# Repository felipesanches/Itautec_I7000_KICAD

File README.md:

Trabalho de levantamento empírico dos esquemáticos do computador Itautec I-7000.

De vez em quando eu atualizo os PDFs:
- i7000.pdf (placa-mãe principal)
- i7000_disk.pdf (placa da interface de controle de disquetes)
- há também uma placa "TELEX" mas não comecei ainda a levantar o esquema dela.

Mas na maior parte do tempo estou só editando no KICAD os arquivos de esquemáticos e PCB por enquanto. Estou tentando me dedicar algumas horas todos os dias para essa tarefa...

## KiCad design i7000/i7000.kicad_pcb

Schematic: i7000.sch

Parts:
C207, C227: C; C_Disc_D3.8mm_W2.6mm_P2.50mm
CN04: Conn_02x30_Counter_Clockwise; Pin_Header_Straight_2x30_Pitch2.54mm
CN05: Conn_02x07_Counter_Clockwise; DIP-14_W7.62mm_Socket
E01: NSC800D-4; DIP-40_W15.24mm
E02: Intel D8202A-1; DIP-40_W15.24mm
E03: M5L8259AP; DIP-28_W15.24mm
E04: 2732; DIP-24_W15.24mm_Socket
E05, E06: 74LS373; DIP-20_W7.62mm
E07: 74LS245; DIP-20_W7.62mm
E08: 74LS257; DIP-16_W7.62mm
E09, E10: 74LS273; DIP-20_W7.62mm
E11, E12: 74LS153; DIP-16_W7.62mm
E13: 74LS138; DIP-16_W7.62mm
E14: 74LS157; DIP-16_W7.62mm
E15: 74LS374; DIP-20_W7.62mm
E16, E17, E18, E19, E20, E21, E22, E23: MCM6665A; DIP-16_W7.62mm
E24, E25, E26: 74LS74; DIP-14_W7.62mm
E27, E28, E29, E38: 74LS04; DIP-14_W7.62mm
E30: 74LS02; DIP-14_W7.62mm
E31, E34: 74LS08; DIP-14_W7.62mm
E32, E33, E36: 74LS32; DIP-14_W7.62mm
E35: 74LS00; DIP-14_W7.62mm
E37: SN74LS07N; DIP-14_W7.62mm
F01: M5L8279P-5; DIP-40_W15.24mm
F02: M5L8253P-5; DIP-24_W15.24mm
F03: TMP8255AP-5; DIP-40_W15.24mm
F04: TMP8251AP; DIP-28_W15.24mm
F05: ADC0808; DIP-28_W15.24mm
F06, F07: 74LS138; DIP-16_W7.62mm
F08, F11, F12: 74LS74; DIP-14_W7.62mm
F9, F10: 74LS163; DIP-16_W7.62mm
F13: 74LS139; DIP-16_W7.62mm
F14: 74LS27; DIP-14_W7.62mm
F15: 74LS00; DIP-14_W7.62mm
F16: 74LS08; DIP-14_W7.62mm
F17: MC1488; DIP-14_W7.62mm
F18, F19: MC1489; DIP-14_W7.62mm
F20: 74LS02; DIP-14_W7.62mm
F21: 74LS04; DIP-14_W7.62mm
F22, F23: SN74LS07N; DIP-14_W7.62mm
G01: MC6845; DIP-40_W15.24mm
G02, G03, G04, G05, G06: 74LS157; DIP-16_W7.62mm
G07, G08: TMM2016AP; DIP-24_W15.24mm
G09, G12: 74LS273; DIP-20_W7.62mm
G10, G11: 74LS245; DIP-20_W7.62mm
G13: 74LS244; DIP-20_W7.62mm
G14: 2732; DIP-24_W15.24mm_Socket
G15, G16, G17: 74LS374; DIP-20_W7.62mm
G18: 74LS166; DIP-16_W7.62mm
G19: Conn_02x08_Counter_Clockwise; DIP-16_W7.62mm
G20, G21: 74LS153; DIP-16_W7.62mm
G22, G23: 74LS174; DIP-16_W7.62mm
G25, G27, G28: 74LS74; DIP-14_W7.62mm
G26: 74LS163; DIP-16_W7.62mm
G29: 74LS20; DIP-14_W7.62mm
G30, G33: 74LS04; DIP-14_W7.62mm
G31, G35: 74LS08; DIP-14_W7.62mm
G32, G34: 74LS32; DIP-14_W7.62mm
G36: 74LS86; DIP-14_W7.62mm
G37: 74128; DIP-14_W7.62mm
G38, G39: 74LS00; DIP-14_W7.62mm
G40, G41: 74S140; DIP-14_W7.62mm
JP03, JP04, JP05: Conn_01x03; Pin_Header_Straight_1x03_Pitch2.54mm
R29, R38, R82, R83: R; R_Axial_DIN0207_L6.3mm_D2.5mm_P10.16mm_Horizontal
XTA2, XTA3, XTA4: Crystal; Crystal_AT310_d3.0mm_l10.0mm_Horizontal_1EP_style2

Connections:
A0: CN04.49, E02.6 (AL0), E06.19 (O7)
A1: CN04.51, E02.8 (AL1), E06.16 (O6)
A2: CN04.50, E02.10 (AL2), E06.15 (O5), F07.1 (A0)
A3: CN04.11, E02.12 (AL3), E06.12 (O4), F07.2 (A1)
A4: CN04.16, E02.14 (AL4), E06.9 (O3), F07.3 (A2), F14.5
A5: CN04.44, E02.16 (AL5), E04.3 (A5), E06.6 (O2), E28.13
A6: CN04.45, E02.18 (AL6), E06.5 (O1), F14.13
A7: CN04.17, E06.2 (O0), E14.3 (I1a), F14.2, G03.14 (I0c)
A8: CN04.15, E02.5 (AH0), E05.19 (O7)
A9: CN04.46, E02.4 (AH1), E05.16 (O6)
A10: CN04.48, E02.3 (AH2), E05.15 (O5)
A11: CN04.12, E02.2 (AH3), E05.12 (O4), G06.13 (I1c)
A12: CN04.47, E02.1 (AH4), E05.9 (O3)
A13: CN04.18, E02.39 (AH5), E05.6 (O2), G06.14 (I0c)
A14: E05.5 (O1), E11.14 (S0), E12.14 (S0)
A15: E05.2 (O0), E11.2 (S1), E12.2 (S1)
CHARGEN_SERIAL_OUT: G18.13 (Qh), G33.1
CN04_07: CN04.7, E13.9 (O6)
CN04_08: CN04.8, E13.10 (O5)
CN04_09: CN04.9, E13.12 (O3)
CN04_10: CN04.10, E13.14 (O1)
CN04_14: CN04.14
CN04_19: CN04.19
CN04_20: CN04.20
CN04_34: CN04.34, E08.15 (OE)
CN04_41: CN04.41
CN04_42: CN04.42
CN04_43: CN04.43
CN04_52: CN04.52, E13.13 (O2)
CN04_53: CN04.53, E13.11 (O4)
CN04_54: CN04.54, E13.7 (O7)
CN05_14: CN05.14, E32.8
CPU_A8: E01.1 (A8), E05.18 (D7)
CPU_A9: E01.2 (A9), E05.17 (D6)
CPU_A10: E01.3 (A10), E05.14 (D5)
CPU_A11: E01.4 (A11), E05.13 (D4)
CPU_A12: E01.5 (A12), E05.8 (D3)
CPU_A13: E01.6 (A13), E05.7 (D2)
CPU_A14: E01.7 (A14), E05.4 (D1)
CPU_A15: E01.8 (A15), E05.3 (D0)
CPU_AD0: E01.12 (AD0), E06.18 (D7), E07.9 (A7)
CPU_AD1: E01.13 (AD1), E06.17 (D6), E07.8 (A6)
CPU_AD2: E01.14 (AD2), E06.14 (D5), E07.7 (A5)
CPU_AD3: E01.15 (AD3), E06.13 (D4), E07.6 (A4)
CPU_AD4: E01.16 (AD4), E06.8 (D3), E07.5 (A3)
CPU_AD5: E01.17 (AD5), E06.7 (D2), E07.4 (A2)
CPU_AD6: E01.18 (AD6), E06.4 (D1), E07.3 (A1)
CPU_AD7: E01.19 (AD7), E06.3 (D0), E07.2 (A0)
D0: CN04.57, E03.11 (D0), E07.11 (B7), E09.3 (D0), E10.3 (D0), E15.2 (O0), E16.2 (D), F01.12 (D0), F02.8 (D0), F03.34 (D0), F04.27 (D0), G27.12 (D)
D1: CN04.56, E03.10 (D1), E07.12 (B6), E09.4 (D1), E10.4 (D1), E15.5 (O1), E17.2 (D), F01.13 (D1), F02.7 (D1), F03.33 (D1), F04.28 (D1)
D2: CN04.5, E03.9 (D2), E07.13 (B5), E09.7 (D2), E10.7 (D2), E15.6 (O2), E18.2 (D), F01.14 (D2), F02.6 (D2), F03.32 (D2), F04.1 (D2)
D3: CN04.55, E03.8 (D3), E07.14 (B4), E09.8 (D3), E10.8 (D3), E15.9 (O3), E19.2 (D), F01.15 (D3), F02.5 (D3), F03.31 (D3), F04.2 (D3)
D4: CN04.6, E03.7 (D4), E07.15 (B3), E09.13 (D4), E10.13 (D4), E15.12 (O4), E20.2 (D), F01.16 (D4), F02.4 (D4), F03.30 (D4), F04.5 (D4)
D5: CN04.4, E03.6 (D5), E07.16 (B2), E09.14 (D5), E10.14 (D5), E15.15 (O5), E21.2 (D), F01.17 (D5), F02.3 (D5), F03.29 (D5), F04.6 (D5)
D6: CN04.58, E03.5 (D6), E07.17 (B1), E09.17 (D6), E10.17 (D6), E15.16 (O6), E22.2 (D), F01.18 (D6), F02.2 (D6), F03.28 (D6), F04.7 (D6)
D7: CN04.3, E03.4 (D7), E07.18 (B0), E09.18 (D7), E10.18 (D7), E15.19 (O7), E23.2 (D), F01.19 (D7), F02.1 (D7), F03.27 (D7), F04.8 (D7)
DRAM_A7: E14.4 (Za), E16.9 (A7), E17.9 (A7), E18.9 (A7), E19.9 (A7), E20.9 (A7), E21.9 (A7), E22.9 (A7), E23.9 (A7)
DRAM_CTRL_AH6: E02.38 (AH6), E11.7 (Za), E13.1 (A0)
DRAM_CTRL_B0: E02.24 (B0), E12.7 (Za), E13.3 (A2), E32.4, E32.12
DRAM_OUT0: E15.3 (D0), E16.14 (Q)
DRAM_OUT1: E15.4 (D1), E17.14 (Q)
DRAM_OUT2: E15.7 (D2), E18.14 (Q)
DRAM_OUT3: E15.8 (D3), E19.14 (Q)
DRAM_OUT4: E15.13 (D4), E20.14 (Q)
DRAM_OUT5: E15.14 (D5), E21.14 (Q)
DRAM_OUT6: E15.17 (D6), E22.14 (Q)
DRAM_OUT7: E15.18 (D7), E23.14 (Q)
E11_pin9_Zb: E11.9 (Zb), E13.2 (A1), E14.2 (I0a)
E38.6_CLK: E38.6
F20.1_CLK: F20.1, G22.9 (Cp), G26.2 (CP), G34.2, G36.5
FF_23.2: G23.7 (Q2), G36.2
G30.6_CLK: G28.3 (C), G30.6, G35.4
GND: CN04.1, CN04.30, CN04.31, CN04.60, E01.20 (GND), E02.20 (GND), E02.25 (B1/OP1), E04.12 (GND), E11.1 (Ea), E11.8 (GND), E11.15 (Eb), E12.1 (Ea), E12.15 (Eb), E16.16 (GND), E17.16 (GND), E18.16 (GND), E19.16 (GND), E20.16 (GND), E21.16 (GND), E22.16 (GND), E23.16 (GND), F01.20 (GND), F04.4 (GND), F14.4, G06.6 (I1b), G06.8 (GND), G07.12 (GND), G08.12 (GND), G14.12 (GND), G36.4, G37.7 (GND)
Gnd: G40.7 (Gnd), G41.7 (Gnd)
IOM: E08.1 (S)
IOR: E08.7 (Zb)
IOW: E08.12 (Zc)
IR3: CN04.25, E03.21 (IR3)
LS157_S: G02.1 (S), G03.1 (S), G04.1 (S), G05.1 (S), G32.1
MEMR: E08.4 (Za)
MEMW: E08.9 (Zd)
unnamed: C207.1, E38.3, R38.2
unnamed: C207.2, E38.2, R29.1
unnamed: C227.1, G30.3, JP04.2, R83.2
unnamed: C227.2, G30.2, R82.1
unnamed: E01.37 (RESET_OUT), E29.11
unnamed: E02.7 (~OUT0), E16.5 (A0), E17.5 (A0), E18.5 (A0), E19.5 (A0), E20.5 (A0), E21.5 (A0), E22.5 (A0), E23.5 (A0)
unnamed: E02.9 (~OUT1), E16.7 (A1), E17.7 (A1), E18.7 (A1), E19.7 (A1), E20.7 (A1), E21.7 (A1), E22.7 (A1), E23.7 (A1)
unnamed: E02.11 (~OUT2), E16.6 (A2), E17.6 (A2), E18.6 (A2), E19.6 (A2), E20.6 (A2), E21.6 (A2), E22.6 (A2), E23.6 (A2)
unnamed: E02.13 (~OUT3), E16.12 (A3), E17.12 (A3), E18.12 (A3), E19.12 (A3), E20.12 (A3), E21.12 (A3), E22.12 (A3), E23.12 (A3)
unnamed: E02.15 (~OUT4), E16.11 (A4), E17.11 (A4), E18.11 (A4), E19.11 (A4), E20.11 (A4), E21.11 (A4), E22.11 (A4), E23.11 (A4)
unnamed: E02.17 (~OUT5), E16.10 (A5), E17.10 (A5), E18.10 (A5), E19.10 (A5), E20.10 (A5), E21.10 (A5), E22.10 (A5), E23.10 (A5)
unnamed: E02.19 (~OUT6), E16.13 (A6), E17.13 (A6), E18.13 (A6), E19.13 (A6), E20.13 (A6), E21.13 (A6), E22.13 (A6), E23.13 (A6)
unnamed: E02.21 (~RAS0), E16.4 (~RAS), E17.4 (~RAS), E18.4 (~RAS), E19.4 (~RAS), E20.4 (~RAS), E21.4 (~RAS), E22.4 (~RAS), E23.4 (~RAS)
unnamed: E02.28 (~WE), E16.3 (~W), E17.3 (~W), E18.3 (~W), E19.3 (~W), E20.3 (~W), E21.3 (~W), E22.3 (~W), E23.3 (~W)
unnamed: E08.3 (I1a), E08.5 (I0b)
unnamed: E08.10 (I1d), E08.14 (I0c)
unnamed: E08.11 (I0d), E08.13 (I1c)
unnamed: E09.2 (Q0), E11.6 (I0a)
unnamed: E09.5 (Q1), E11.10 (I0b)
unnamed: E09.6 (Q2), E12.6 (I0a)
unnamed: E09.9 (Q3), E12.10 (I0b)
unnamed: E09.12 (Q4), E11.5 (I1a)
unnamed: E09.15 (Q5), E11.11 (I1b)
unnamed: E09.16 (Q6), E12.5 (I1a)
unnamed: E09.19 (Q7), E12.11 (I1b)
unnamed: E10.2 (Q0), E11.4 (I2a)
unnamed: E10.5 (Q1), E11.12 (I2b)
unnamed: E10.6 (Q2), E12.4 (I2a)
unnamed: E10.9 (Q3), E12.12 (I2b)
unnamed: E10.12 (Q4), E11.3 (I3a)
unnamed: E10.15 (Q5), E11.13 (I3b)
unnamed: E10.16 (Q6), E12.3 (I3a)
unnamed: E10.19 (Q7), E12.13 (I3b)
unnamed: E13.6 (E3), E32.10, E32.13, E36.5
unnamed: E14.10 (I1d), E14.11 (I0d), E32.6
unnamed: E26.11 (C), E27.12
unnamed: E27.1, F02.10 (OUT0)
unnamed: E32.1, E32.9
unnamed: E38.1, R29.2, XTA2.1
unnamed: E38.4, E38.5, R38.1, XTA2.2
unnamed: F02.11 (G0), F02.14 (G1)
unnamed: F02.13 (OUT1), F17.9
unnamed: F02.15 (CLK1), F02.18 (CLK2)
unnamed: F02.17 (OUT2), F17.2
unnamed: F07.4 (E1), F07.5 (E2)
unnamed: F07.6 (E3), F15.3
unnamed: F07.14 (O1), F13.1 (E)
unnamed: F13.6 (O2), G33.13
unnamed: F13.15 (E), F15.6
unnamed: F14.1, F16.6
unnamed: F14.6, F15.5
unnamed: F14.12, F15.1, F15.4
unnamed: F20.2, G35.6
unnamed: F20.3, G35.11
unnamed: G06.3 (I1a), G34.6
unnamed: G06.9 (Zd), G28.13 (~R), G30.11
unnamed: G06.12 (Zc), G30.13, G31.2
unnamed: G06.15 (E), G27.8 (~Q)
unnamed: G09.2 (Q0), G13.2 (I0a), G14.5 (A3)
unnamed: G09.5 (Q1), G13.4 (I1a), G14.4 (A4)
unnamed: G09.6 (Q2), G13.6 (I2a), G14.3 (A5)
unnamed: G09.9 (Q3), G13.8 (I3a), G14.2 (A6)
unnamed: G09.12 (Q4), G13.11 (I0b), G14.1 (A7)
unnamed: G09.15 (Q5), G13.13 (I1b), G14.23 (A8)
unnamed: G09.16 (Q6), G13.15 (I2b), G14.22 (A9)
unnamed: G09.19 (Q7), G13.17 (I3b), G14.19 (A10)
unnamed: G10.19 (CE), G32.6
unnamed: G11.19 (CE), G32.8
unnamed: G13.3 (O3b), G14.17 (Q7), G18.14 (H)
unnamed: G13.5 (O2b), G14.16 (Q6), G18.12 (G)
unnamed: G13.7 (O1b), G14.15 (Q5), G18.11 (F)
unnamed: G13.9 (O0b), G14.14 (Q4), G18.10 (E)
unnamed: G13.12 (O3a), G14.13 (Q3), G18.5 (D)
unnamed: G13.14 (O2a), G14.11 (Q2), G18.4 (C)
unnamed: G13.16 (O1a), G14.10 (Q1), G18.3 (B)
unnamed: G13.18 (O0a), G14.9 (Q0), G18.2 (A)
unnamed: G19.7, G36.6
unnamed: G27.2 (D), G27.6 (~Q), G35.13
unnamed: G27.10 (~S), G28.1 (~R), G28.4 (~S), G28.10 (~S), G28.12 (D)
unnamed: G27.11 (C), G33.12
unnamed: G28.5 (Q), G35.12
unnamed: G29.8, G35.2
unnamed: G30.1, JP03.2, R82.2
unnamed: G30.4, G30.5, R83.1
unnamed: G30.10, G31.1, G31.4, G31.9
unnamed: G30.12, G31.5
unnamed: G31.10, G31.12
unnamed: G31.13, G32.13
unnamed: G32.3, G32.5, G32.9
unnamed: G33.2, G35.1
unnamed: G34.3, G36.9
unnamed: G34.4, G36.3
unnamed: G35.3, G36.1
unnamed: G35.5, G36.10
unnamed: JP03.1, XTA4.2
unnamed: JP03.3, XTA3.2
unnamed: JP04.1, XTA4.1
unnamed: JP04.3, XTA3.1
RA0: G01.38 (RA0), G14.8 (A0), G29.9
RA1: G01.37 (RA1), G14.7 (A1), G29.10
RA2: G01.36 (RA2), G14.6 (A2), G29.12
RA3: G01.35 (RA3), G34.5
RA4: G01.34 (RA4)
RD: E08.2 (I0a), E08.6 (I1b), E27.13
REG1_BIT4: G15.12 (O4), G29.13
RESET_OUT_DELAYED: CN04.23, E29.8, G30.9
TOGGLE_FF_G27A: F07.15 (O0), G27.3 (C)
VCC: CN04.2, CN04.29, CN04.32, CN04.59, E01.40 (VCC), E02.40 (VCC), E16.8 (VCC), E17.8 (VCC), E18.8 (VCC), E19.8 (VCC), E20.8 (VCC), E21.8 (VCC), E22.8 (VCC), E23.8 (VCC), F01.40 (VCC), F04.26 (VCC), G07.24 (VCC), G08.24 (VCC), G37.14 (VCC)
Vcc: E04.24 (Vcc), G14.24 (Vcc), G40.14 (Vcc), G41.14 (Vcc)
~A5: E28.12, F14.3, F15.2
~CHARGEN_ROM_G: G14.20 (~G), G15.1 (OE), G27.9 (Q)
~CPU_RESET_OUT: E09.1 (~Mr), E10.1 (~Mr), E29.9, E29.10
~CPU_RSTB: E01.23 (~RSTB), E27.2
~DRAM_CAS: E14.9 (Zd), E16.15 (~CAS), E17.15 (~CAS), E18.15 (~CAS), E19.15 (~CAS), E20.15 (~CAS), E21.15 (~CAS), E22.15 (~CAS), E23.15 (~CAS)
~DRAM_CTRL_CAS: E02.27 (~CAS), E32.5
~DRAM_CTRL_WR: E02.31 (~WR), E36.6
~GFX_SRAM1_CS: G31.3, G32.4
~GFX_SRAM2_CS: G31.6, G32.10
~I8251_CS: F04.11 (~CS), F13.11 (O1)
~KBDC_CS: F01.22 (~CS), F13.12 (O0)
~MAINCPU_ROM_E: E04.18 (~E)
~MAINCPU_ROM_G: E04.20 (~G)
~PIC_CS: E03.1 (~CS~), F07.10 (O5)
~PIT8253_CS: F02.21 (~CS~), F07.9 (O6)
~PPI_I8255_CS: F03.6 (~CS~), F07.7 (O7)
~RESET_OUT_DELAYED: G27.1 (~R), G27.13 (~R), G30.8
~WE_CN04_40: CN04.40, E36.4, G10.1 (A->B), G11.1 (A->B), G29.5

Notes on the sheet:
READ
WRITE
FOOTPRINT NAO POPULADO NA PCB DO I-7000 G
G24.7
G24.9
FIXME: The pinout of this symbol does not match its footprint on kicad_pcb
TODO: C225
pode isso?!
REGISTER #1
FLIP-FLOPS #1
Not installed on ITAUTEC I-7000
Actual intended parts are only a guess based on apparent pinout.
REGISTER #2
REGISTER #3
G19 not installed
FLIP-FLOPS #2
JP01: [1-2]-3 JP02: [1-2] JP03: 1-[2-3] JP04: 1-[2-3] JP05: [1-2]-3 JP06: 1-[2-3] JP07: [1-2]-3 JP08: 1-[2-3] JP09: [1-2]-3 JP10: [1-2]-3 JP11: 1-[2-3] JP12: 1-[2-3] JP13: 1-[2-3] JP14: 1-[2-3] JP15: 1-[2-3] DP01: 1 - ON 2 - ON 3 - OFF 4 - ON 5 - ON 6 - ON 7 - OFF 8 - ON
8-Bit μP Compatible A/D Converters with 8-Channel Multiplexer

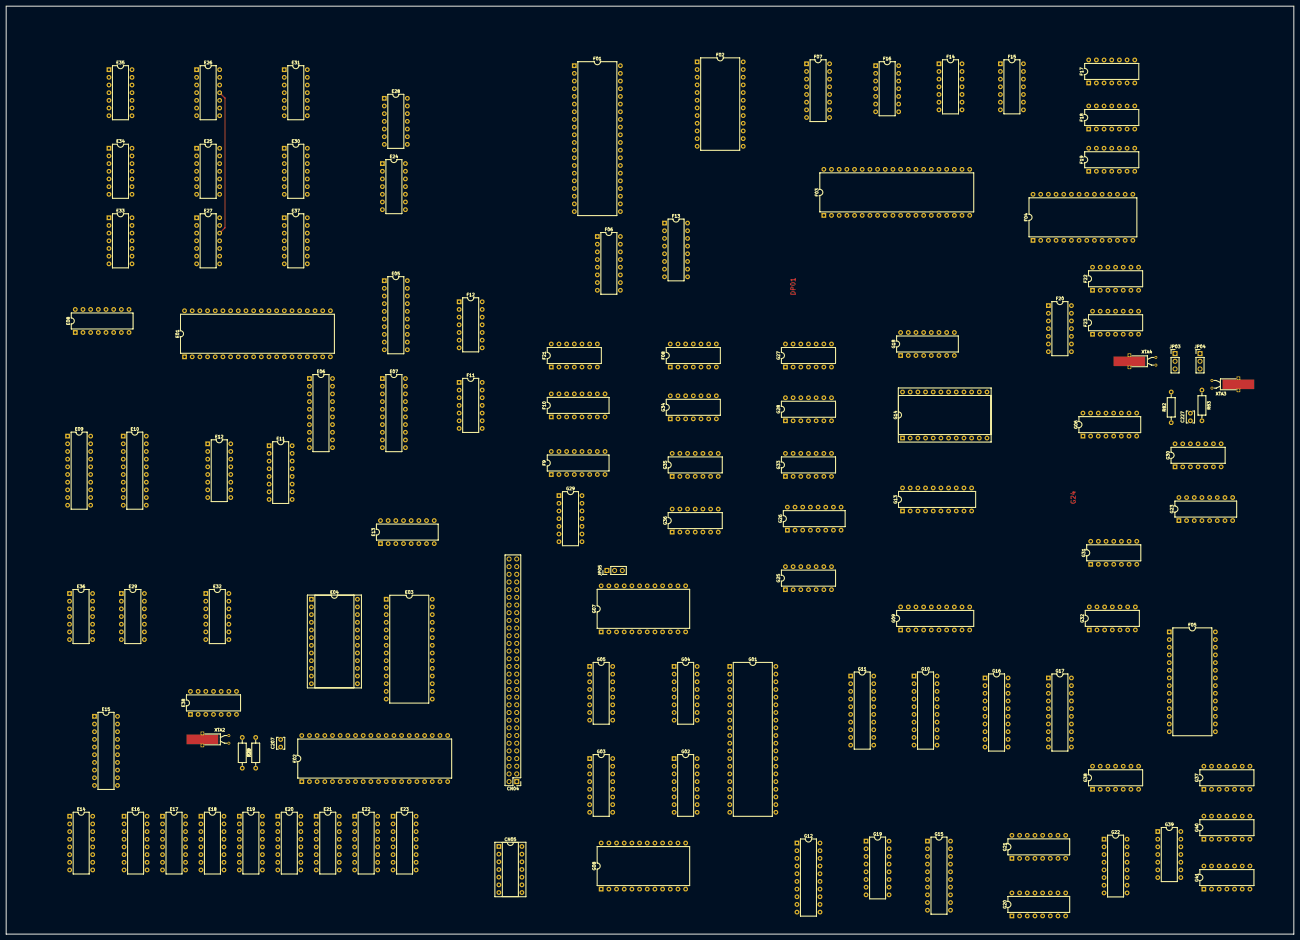
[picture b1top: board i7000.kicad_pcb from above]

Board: 2 copper layers, 426.0 x 307.0 mm, 115 parts (0 on the bottom side), 193 nets.

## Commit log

2020-11-16 esboco inicial dos esquematicos de algumas partes do circuito do I7000
2020-11-19 transcricao de ontem de madrugada
2020-11-19 mais um pouco hoje
2020-11-20 creating a library of symbols for chips used in the Itautec I7000 but still not available in KICAD libraries. We should contribute these later to the project.
2020-11-21 Mais um símbolo novo pro KICAD: Programmable Keyboard/display controler M5L8279P-5
2020-11-21 TMP8251AP - Programmable Communication Interface (Serial Port Controller)
2020-11-21 wip...
2020-11-23 DRAM
2021-05-28 Not sure what was that, but these changes were sitting here on my local copy since the last time I worked on this schematic drawing effort. I guess it is safer to commit it separately before working 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
2021-05-28 anotando alguns componentes que estavam sem referencias
2021-05-28 splitting drawing into one schematic per PCB
2021-05-28 iniciando o posicionamento de componentes da PCB principal
2021-05-29 mais um pedacinho do circuito
2021-05-29 atualizando footprints no layout da PCB
2021-05-30 avanços de ontem
2021-05-30 update footprints and PCB layout
2021-05-31 avanços de hoje ;-)
2021-05-31 atualizando os PDFs de esquemáticos e adicionando um "LEIAME" ;-)
2021-05-31 É melhor o README.md ficar na raiz do repo
2022-05-18 local modifications left on my working copy uncommitted since the last time I worked on this project... I'm blindly commiting this in the hope it is good stuff ;-) (crossing fingers here LOL)
2022-05-18 symbol drawing for TMM2016AP (SRAM)
    and added a few more symbols on the schematics
2022-05-18 use Package_DIP footprints instead of the older ones called Housings_DIP
2022-05-19 a few more chips
2022-05-20 coloquei todos os chips no esquemático e na PCB. Agora falta "só" mapear os sinais...
